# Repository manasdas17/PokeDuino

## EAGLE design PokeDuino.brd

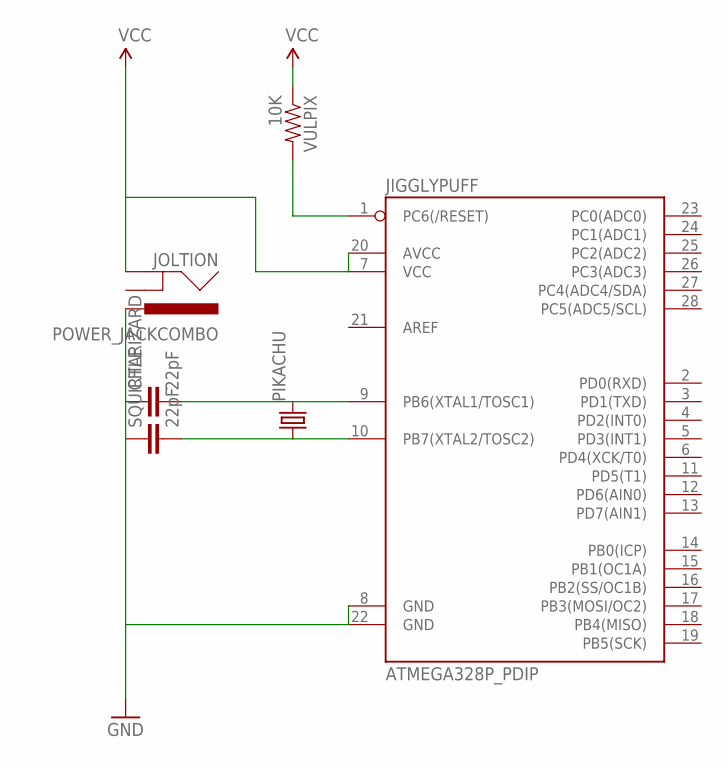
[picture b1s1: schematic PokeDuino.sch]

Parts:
CHARIZARD: 22pF; CAP-PTH-5MM
JIGGLYPUFF: ATMEGA328P_PDIP; DIL28-3
JOLTION: POWER_JACKCOMBO; POWER_JACK_COMBO
PIKACHU: CRYSTALHC49UV; HC49U-V
SQUIRTLE: 22pF; CAP-PTH-5MM
VULPIX: 10K; AXIAL-0.4

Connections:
unnamed: JIGGLYPUFF.10 (PB7(XTAL2/TOSC2)), PIKACHU.1, SQUIRTLE.2
unnamed: JIGGLYPUFF.1 (PC6(/RESET)), VULPIX.P$2 (2)
unnamed: CHARIZARD.1, JIGGLYPUFF.8 (GND), JIGGLYPUFF.22 (GND), JOLTION.POWER (PWR), SQUIRTLE.1
unnamed: CHARIZARD.2, JIGGLYPUFF.9 (PB6(XTAL1/TOSC1)), PIKACHU.2
VCC: JIGGLYPUFF.7 (VCC), JIGGLYPUFF.20 (AVCC), JOLTION.GND@1 (GND), VULPIX.P$1 (1)

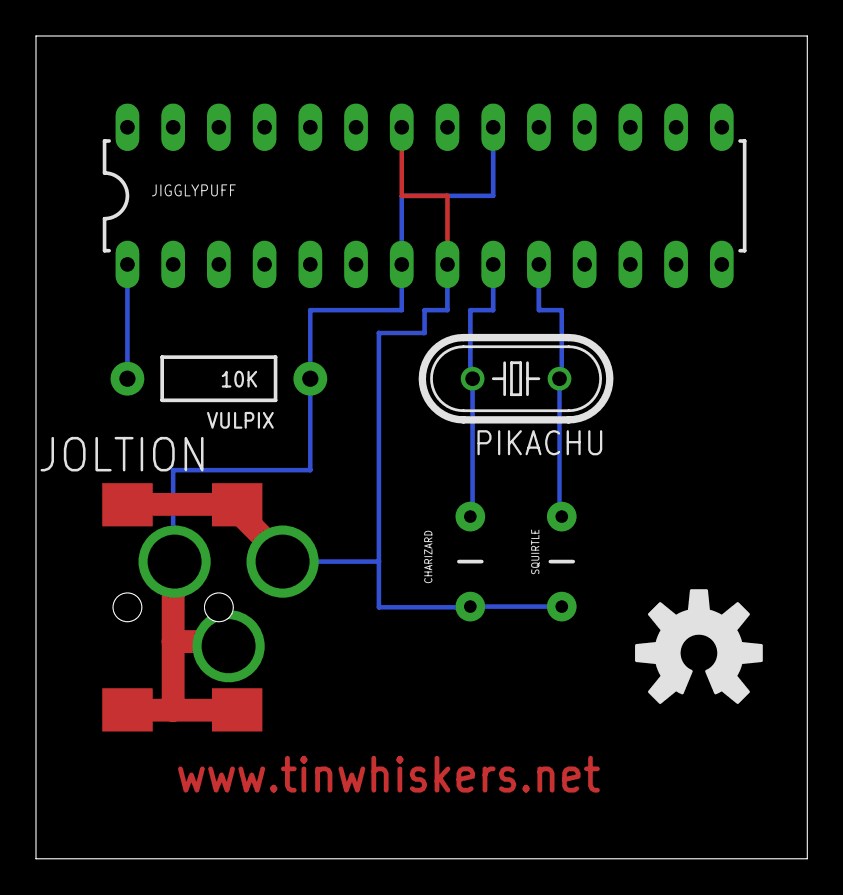
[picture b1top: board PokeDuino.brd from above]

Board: 2 copper layers, 42.9 x 45.7 mm, 7 parts (0 on the bottom side), 5 nets.

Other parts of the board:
U$1: OSHW-LOGO-L

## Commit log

2014-02-15 PokeDuino Schematic and Board

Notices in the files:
parts and their libraries:
SparkFun-DigitalIC: Licensing: CC v3.0 Share-Alike You are welcome to use this library for commercial purposes.
